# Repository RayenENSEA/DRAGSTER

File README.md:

# Rapport Projet DRAGSTER
#  Introduction
  L'objectif de ce projet consiste en la réalisation d'un Dragster, un type de véhicule de course extrêmement rapide, conçu spécifiquement pour des accélérations fulgurantes sur de courtes distances. Ces machines de course impressionnantes sont souvent propulsées par des moteurs surpuissants, capables de générer une grande puissance en un temps très court. 
 
 L'aspect clé de notre projet est l'autonomie du Dragster. Contrairement à un véhicule télécommandé traditionnel, qui dépend d'un opérateur pour le contrôle, notre dragster sera muni d'un bouton poussoir ainsi que de capteurs tels qu'un accéléromètre afin d'assurer une trajectoire droite déclenchée automatiquement sur quelques mètres.
  
# Objectifs du projet
* Réaliser un PCB fonctionnel permettant d'être relié aux composants du Dragster
* Faire fonctionner le véhicule pour qu'il puisse avancer de manière autonome
* Faire avancer le véhicule sur une trajectoire droite de 10m
* Faire avancer le véhicule sur une trajectoire droite de 10m le plus rapidement possible

# Ressources utilisées
## Matériel à disposition :
* Robitronic Moteur Brushless R01230 3000kV
* Gens Ace Batterie 11,1V GEA45003S60X9
* Servomoteur Dynamiel XL-320
* Microcontrôleur STM32L412KBTx
* Variateur Brushless R01221 50A
* Châssis du Dragster ainsi que les deux roues arrière et la roue avant plus petite que les deux autres

## Ressources numériques :
* Github
* KiCad pour la réalisation des schematics et PCB 
* STM32CubeIDE pour la réalisation de la partie Software
* Draw.io pour la réalisation de schémas
* Redmine pour distribuer les tâches et contruire le diagramme de Gantt

# Réalisation

## PCB et Schematics
À partir du schéma hardware ainsi que les composants énoncés dans la datasheet, il a été possible de réaliser un schematic à l'aide de Kicad. Ce schematic reprend les fonctions énoncées dans le schéma hardware. Nous avons eu besoin de consulter les datasheets pour réaliser les montages impliquant notamment les régulateurs à découpage MAX5033DUSA+ pour les tensions 7.4 V et  3.3 V.

Le schéma hardware est disponible sous le nom "Schéma Hardaware.drawio" dans le dossier suivant : https://github.com/RayenENSEA/DRAGSTER/tree/main/Hardware.

## Régulateur à découpage
Comme détaillé precedemment, notre projet comprennait la réalisation de 2 régulateurs pour obtenir les tensions 7.4 V et  3.3 V.
Nos professeurs nous ont conseillés d'opter pour des régulateurs à découpage plutôt que pour des régulateurs linéaires LDO.

En effet, bien que plus compliqués à réaliser, les régulateurs à découpage ont un rendement compris entre 80 % et 90 %, bien plus grand que les régulateurs linéaires. Ces derniers ont en plus la mauvaise caractéristique de dissiper beaucoup de chaleur.

Cependant, la compléxité des régulateurs à découpage est plus élevée car ils necessitent plusieurs composants pour leur réalisation : des inductances, des diodes et des condensateurs de filtrage ainsi que le circuit intégré.
C'est donc pour son efficacité que le régulateur à découpage a plus judicieusement été choisi pour réaliser notre projet.

## Partie software
Ce projet permet de contrôler à la fois un servomoteur Dynamixel XL-320 et un driver de moteur synchrone 50A en utilisant la carte STM32L412KBT3. 
Il utilise l'environnement de développement STM32CubeIDE. 
Voici la description détaillée :  https://github.com/RayenENSEA/DRAGSTER/blob/main/Software/README.md

## Notes en cours de projet
* Liste des composants : https://github.com/RayenENSEA/DRAGSTER/wiki/Liste-des-composants
* Notes globales : https://github.com/RayenENSEA/DRAGSTER/wiki/Notes
* Point avec les professeurs : https://github.com/RayenENSEA/DRAGSTER/wiki/Point-prof-11.04

# Difficultés rencontrées 
* Nous avons fait face à plusieurs difficultés pour la réalisation du PCB, notamment par rapport au routage au vu de la taille de la carte et des composants à utiliser
* Il y a eu des difficultés au moment de tester la carte puisque nous avons constater pendant la soudure des composants des défauts compromettant le fonctionnement de la carte
* En raison du retard de la carte PCB, nous rencontrons des difficultés pour tester tous les codes que nous avons développés avec les autres composants. Cela nous a empêché de réaliser l'étude d'asservissement et d'améliorer les performances des moteurs.
* Les séances de soudure étaient très enrichissantes, nous avons découvert la technique de soudage sur PCB. En soudant des petits composants, il y a eu quelques court-circuits au début.
* Le professeur nous a ensuite conseillé d'essayer une 2ème version du PCB (plaque sans le vernis) pour réduire les risques de dysfonctionnement de la carte.
* Les régulateurs de tension ne fonctionnaient pas comme nous le souhaitions lorsqu'ils étaient à vide ou qu'il y avait une petite charge. Il y avait de courtes phases de régulation puis la tension affichée était celle de l'alimentation.
* Nous avons quand même tenu à terminer le soudage des composants sur la carte pour observer le résultat final et plusieurs composants comme les LEDs fonctionnaient comme prévu.

# Enjeux environnementaux
* 1 - Votre projet favorise-t-il des changements dans les modes de production et de consommation en vue de les rendre plus viables et plus responsables sur les plans social et environnemental ?
 
Notre projet peut avoir un certain impact en faveur de changements dans les modes de production et de consommation premièrement par l'utilisation d'un Dragster fonctionnant avec un moteur éléctrique autonome. L'utilisation de moteurs éléctrique permet la réduction d'émission de gaz à effet de serre et permet donc de démontrer l'efficacité des technologies de propulsion éléctrique. L'exploitation des ressources utilisées permet au projet de pouvoir être réutilisé dans d'autres circonstances et sensibilise donc à la mobilité éléctrique en mettant l'accent sur la technologie de pointe et les performances écologiques concernant la mobilité durable.

* 2 - Quelle réflexion avez-vous mené au cours de ce projet autour de la réutilisation possible d'éléments matériels après votre projet ?

Lors de ce projet, nous avons pris en compte plusieurs points concernant cette question. En effet, la conception du Dragster est modulaire, ce qui rend plus facile le démontage
et la récupération éventuelle de composants individuels qui peuvent être réutilisés dans d'autres projets ou réparer si besoin. L'usage de composant standardisé comme le microcontrôleur permet de maximiser le potentiel de réutilisation, les composants peuvent être utilisés dans de nombreux projets ce qui augmente la chance de les intégrer dans d'autres systèmes à l'avenir.
La documentation nécessaire concernant les schematics, les codes sources et les instructions de montages peuvent également permettre une réutilisation approprié des éléments matériels du projet.
Finalement, si des matériaux ne peuvent être recyclés ou réparer, il est possible de les recycler correctement, comme les métaux ou les circuits imprimés pouvant être transformés en nouvelles ressources dans l'optique de réduire les déchets éléctroniques.

# Présentation soutenance

[Dragster project.pdf](https://github.com/RayenENSEA/DRAGSTER/files/11707936/Dragster.project.pdf)

Lors de la présentation de notre projet, nous avons réussi à montrer une maquette complète avec les différents composants et à les alimenter avec les bonnes tensions. 

En effet, nous avons eu la bonne surprise de découvrir que les régulateurs agissaient de manière correcte lorsque nous avons connecté toutes les pièces entre elles. De plus, après un ultime essai de téléversement du code vers le microcontrolleur, celui-ci a également fonctionné, ce qui nous a permis de réaliser une démonstration du bon fonctionnement d'une partie de la maquette et une suite possible d'évolution et d'amélioration du Dragster project.

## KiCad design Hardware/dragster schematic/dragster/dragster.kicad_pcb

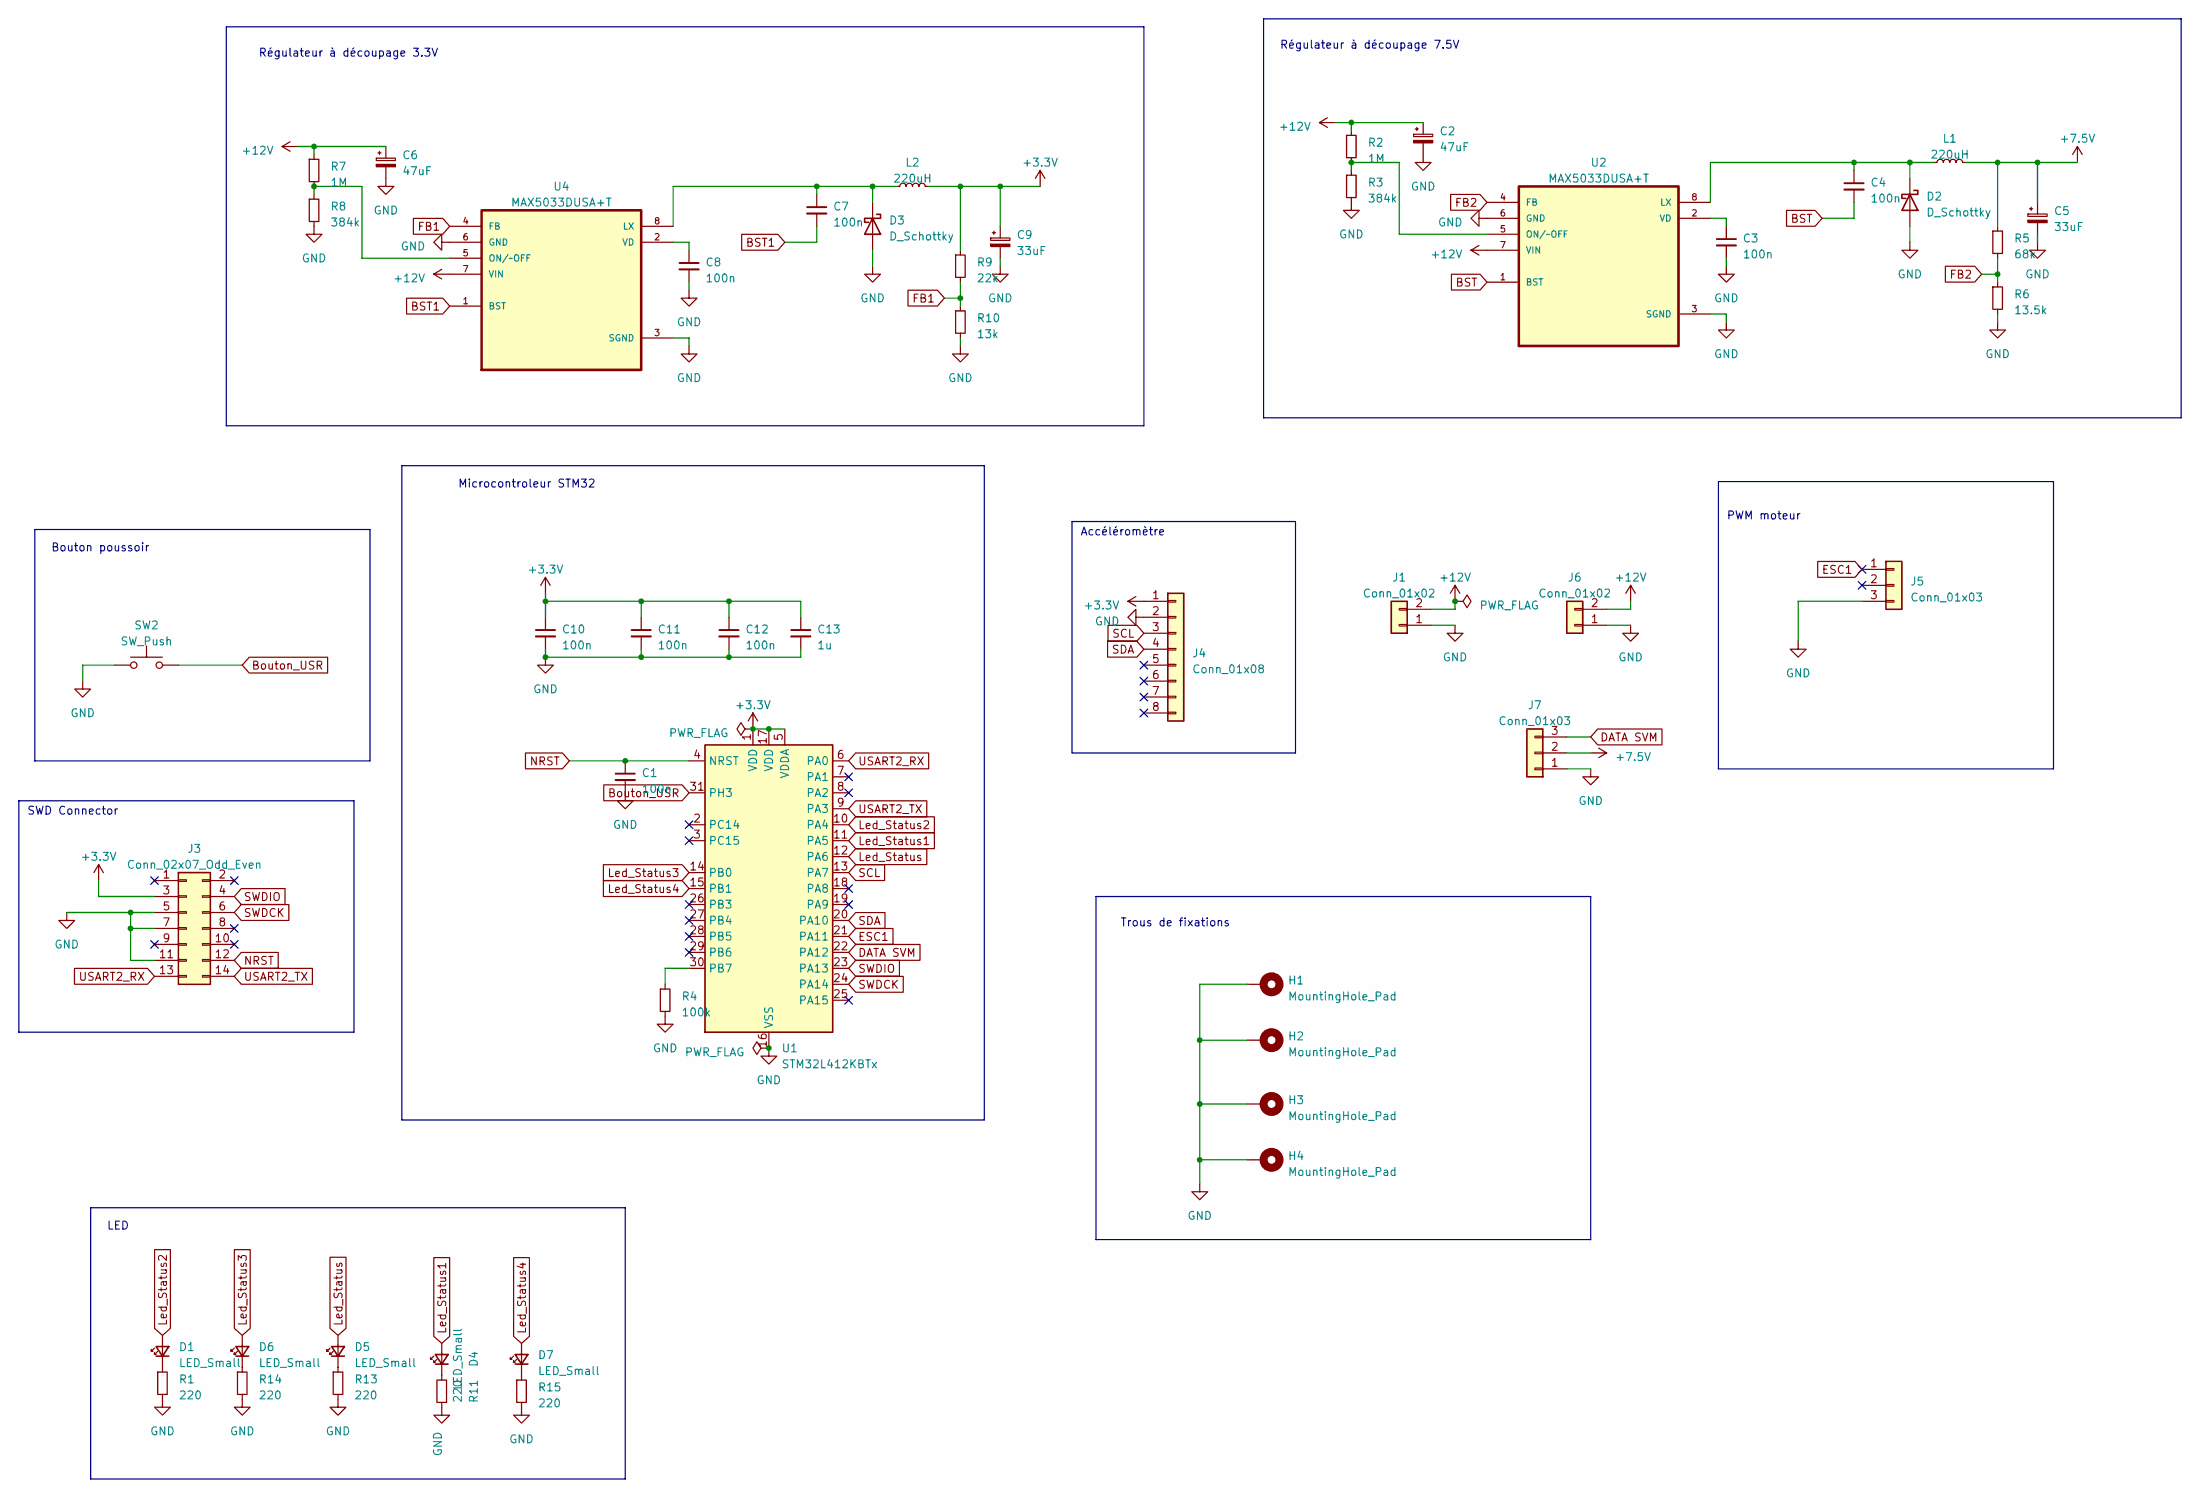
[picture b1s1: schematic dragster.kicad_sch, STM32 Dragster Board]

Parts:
C1, C3, C4, C7, C8, C10, C11, C12: 100n; C_0603_1608Metric_Pad1.08x0.95mm_HandSolder
C2, C6: 47uF; C_Elec_6.3x5.4
C5, C9: 33uF; C_Elec_6.3x5.4
C13: 1u; C_0603_1608Metric_Pad1.08x0.95mm_HandSolder
D1, D4, D5, D6, D7: LED_Small; LED_0603_1608Metric_Pad1.05x0.95mm_HandSolder
D2, D3: D_Schottky; D_2114_3652Metric_Pad1.85x3.75mm_HandSolder
H1, H2, H3, H4: MountingHole_Pad; MountingHole_3.2mm_M3_DIN965_Pad
J1, J6: Conn_01x02; AMASS_XT60-M_1x02_P7.20mm_Vertical
J3: Conn_02x07_Odd_Even; PinHeader_2x07_P1.27mm_Vertical_SMD
J4: Conn_01x08; PinSocket_1x08_P2.54mm_Vertical
J5, J7: Conn_01x03; JST_XH_B3B-XH-A_1x03_P2.50mm_Vertical
L1, L2: 220uH; L_12x12mm_H6mm
R1, R11, R13, R14, R15: 220; R_0603_1608Metric_Pad0.98x0.95mm_HandSolder
R2, R7: 1M; R_0603_1608Metric_Pad0.98x0.95mm_HandSolder
R3, R8: 384k; R_0603_1608Metric_Pad0.98x0.95mm_HandSolder
R4: 100k; R_0603_1608Metric_Pad0.98x0.95mm_HandSolder
R5: 68k; R_0603_1608Metric_Pad0.98x0.95mm_HandSolder
R6: 13.5k; R_0603_1608Metric_Pad0.98x0.95mm_HandSolder
R9: 22k; R_0603_1608Metric_Pad0.98x0.95mm_HandSolder
R10: 13k; R_0603_1608Metric_Pad0.98x0.95mm_HandSolder
SW2: SW_Push; SW_SPST_B3U-1000P
U1: STM32L412KBTx; LQFP-32_7x7mm_P0.8mm
U2, U4: MAX5033DUSA+T; SOIC-8_3.9x4.9mm_P1.27mm

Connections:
+3.3V: C9.1, C10.1, C11.1, C12.1, C13.1, J3.3, J4.1, L2.2, R9.1, U1.1 (VDD), U1.5 (VDDA), U1.17 (VDD)
+7.5V: C5.1, J7.2, L1.2, R5.1
+12V: C2.1, C6.1, J1.2, J6.2, R2.1, R7.1, U2.7 (VIN), U4.7 (VIN)
BST: C4.2, U2.1 (BST)
BST1: C7.2, U4.1 (BST)
Bouton_USR: SW2.2, U1.31 (PH3)
DATA SVM: J7.3, U1.22 (PA12)
ESC1: J5.1, U1.21 (PA11)
FB1: R9.2, R10.1, U4.4 (FB)
FB2: R5.2, R6.1, U2.4 (FB)
GND: C1.2, C2.2, C3.2, C5.2, C6.2, C8.2, C9.2, C10.2, C11.2, C12.2, C13.2, D2.2 (A), D3.2 (A), H1.1, H2.1, H3.1, H4.1, J1.1, J3.5, J3.7, J3.11, J4.2, J5.3, J6.1, J7.1, R1.2, R3.2, R4.2, R6.2, R8.2, R10.2, R11.1, R13.2, R14.2, R15.2, SW2.1, U1.16 (VSS), U1.32 (VSS), U2.3 (SGND), U2.6 (GND), U4.3 (SGND), U4.6 (GND)
Led_Status: D5.2 (A), U1.12 (PA6)
Led_Status1: D4.2 (A), U1.11 (PA5)
Led_Status2: D1.2 (A), U1.10 (PA4)
Led_Status3: D6.2 (A), U1.14 (PB0)
Led_Status4: D7.2 (A), U1.15 (PB1)
NRST: C1.1, J3.12, U1.4 (NRST)
unnamed: D1.1 (K), R1.1
unnamed: C4.1, D2.1 (K), L1.1, U2.8 (LX)
unnamed: C7.1, D3.1 (K), L2.1, U4.8 (LX)
unnamed: D4.1 (K), R11.2
unnamed: D5.1 (K), R13.1
unnamed: D6.1 (K), R14.1
unnamed: D7.1 (K), R15.1
unnamed: R4.1, U1.30 (PB7)
unnamed: R2.2, R3.1, U2.5 (ON/~OFF)
unnamed: C3.1, U2.2 (VD)
unnamed: R7.2, R8.1, U4.5 (ON/~OFF)
unnamed: C8.1, U4.2 (VD)
SCL: J4.3, U1.13 (PA7)
SDA: J4.4, U1.20 (PA10)
SWDCK: J3.6, U1.24 (PA14)
SWDIO: J3.4, U1.23 (PA13)
USART2_RX: J3.13, U1.6 (PA0)
USART2_TX: J3.14, U1.9 (PA3)

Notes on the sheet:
Régulateur à découpage 3.3V
PWM moteur
LED
Régulateur à découpage 7.5V
Accéléromètre
Microcontroleur STM32
Trous de fixations
Bouton poussoir
SWD Connector

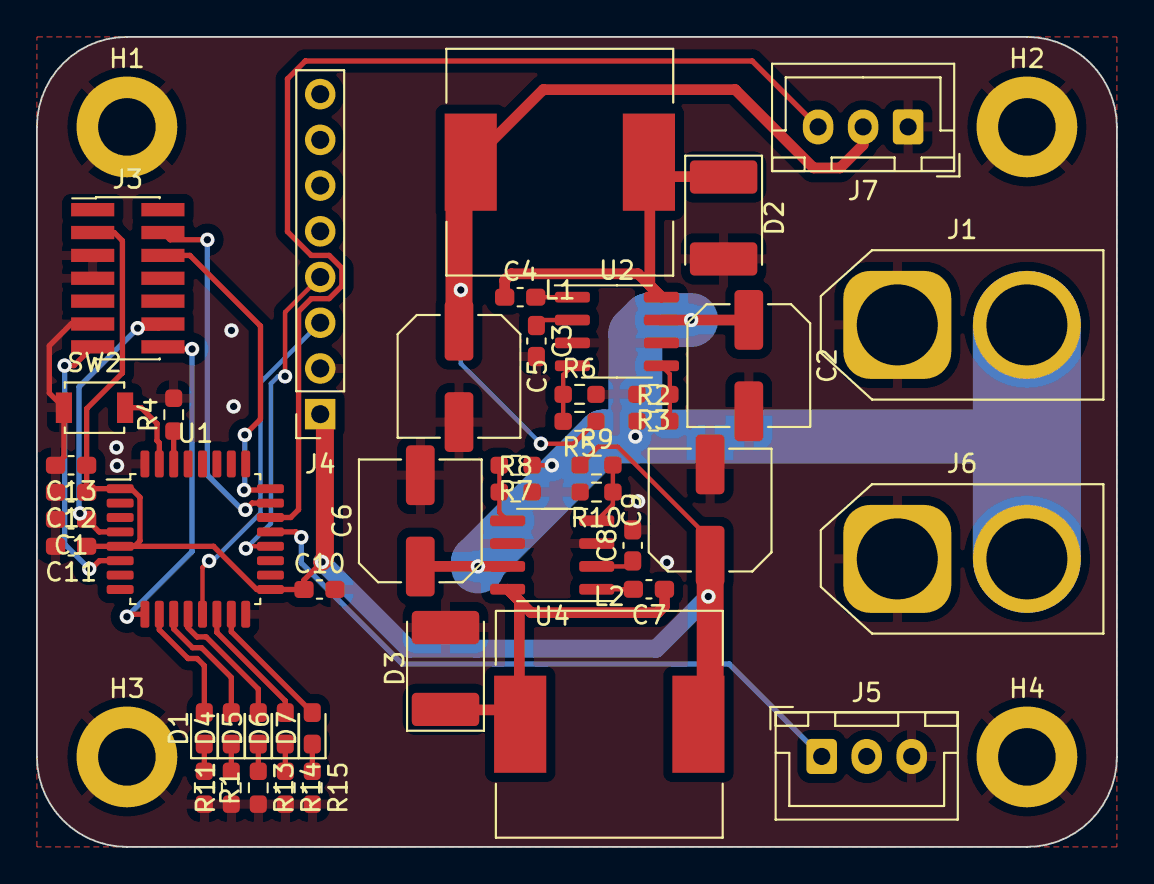
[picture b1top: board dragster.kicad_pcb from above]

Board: 2 copper layers, 60.0 x 45.0 mm, 50 parts (0 on the bottom side), 35 nets.

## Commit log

2023-04-03 diagramme
2023-04-03 Diagramme de Cahier de Charge
2023-04-03 cahier de charge
2023-04-03 cahier de charge.drawio
2023-04-03 cahier de charge (en cours)
2023-04-03 diag.png
2023-04-07 add folders
2023-04-09 Ajouté(e) Schéma Hardaware.drawio
2023-04-09 Mettre à jour Schéma Hardaware.drawio
2023-04-09 Mettre à jour cahier de charge.drawio.png
2023-04-11 SchémaExplicatifDuSoftware.png
2023-04-11 Mettre à jour SchémaExplicatifDuSoftware.png
2023-04-17 correction
2023-05-09 Create XL-320
2023-05-15 Create proj
2023-05-30 Create Rapport
